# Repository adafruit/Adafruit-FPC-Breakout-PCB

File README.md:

## Adafruit FPC Breakout for Raspberry Pi 5 DSI or RP2350 HSTX - 22 Pin 0.5mm PCB

<a href="http://www.adafruit.com/products/6014"><br/>
Click here to purchase one from the Adafruit shop</a>

PCB files for the Adafruit FPC Breakout for Raspberry Pi 5 DSI or RP2350 HSTX - 22 Pin 0.5mm. 

Format is EagleCAD schematic and board layout
* https://www.adafruit.com/product/6014

### Description

This little breakout board is specifically designed for use with Raspberry Pi 5 or our RP2350 boards that have an 'HSTX' connector. These devices use a semi-standard FPC connector to pipe high speed data for video transmission over differential pairs. But maybe you want to make a custom setup or adapt to a different product? This doohickey is your pal.

Basically, you can use a 22-pin 0.5mm pitch FPC cable to connect between the two boards to get access to the four (Pi 5) or three (HSTX) differential data channels, plus the differential clock. There's also 3.3V power output, I2C, and two GPIO. We placed a fairly big ground plane and we did our best to route the signals cleanly but any time you solder wires or use a bread/perf-board with high-speed signal there's a risk of signal degradation!

Each order comes with one breakout board, 22-pin FPC cable is not included.

### License

Adafruit invests time and resources providing this open source design, please support Adafruit and open-source hardware by purchasing products from [Adafruit](https://www.adafruit.com)!

Designed by Limor Fried/Ladyada for Adafruit Industries.

Creative Commons Attribution/Share-Alike, all text above must be included in any redistribution. 
See license.txt for additional details.

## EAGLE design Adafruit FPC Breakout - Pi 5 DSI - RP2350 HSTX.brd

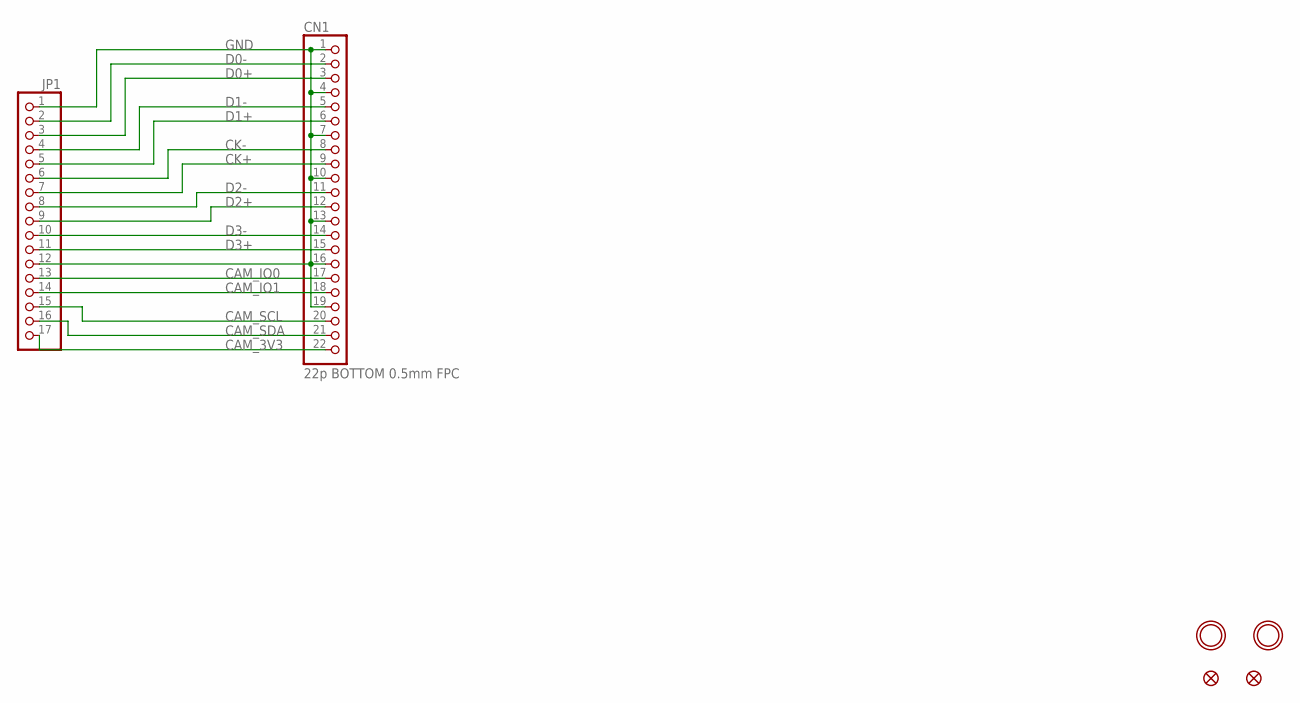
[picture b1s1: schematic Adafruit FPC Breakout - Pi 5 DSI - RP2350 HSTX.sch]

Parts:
CN1: 22p BOTTOM 0.5mm FPC; FPC_22PIN
FID1, FID2: FIDUCIAL_1MM
JP1: HEADER-1X17; 1X17_ROUND70
U$2, U$3: MOUNTINGHOLE2.5; MOUNTINGHOLE_2.5_PLATED

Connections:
CAM_3V3: CN1.22, JP1.17
CAM_IO0: CN1.17, JP1.13
CAM_IO1: CN1.18, JP1.14
CAM_SCL: CN1.20, JP1.15
CAM_SDA: CN1.21, JP1.16
CK+: CN1.9, JP1.7
CK-: CN1.8, JP1.6
D0+: CN1.3, JP1.3
D0-: CN1.2, JP1.2
D1+: CN1.6, JP1.5
D1-: CN1.5, JP1.4
D2+: CN1.12, JP1.9
D2-: CN1.11, JP1.8
D3+: CN1.15, JP1.11
D3-: CN1.14, JP1.10
GND: CN1.1, CN1.4, CN1.7, CN1.10, CN1.13, CN1.16, CN1.19, JP1.1, JP1.12

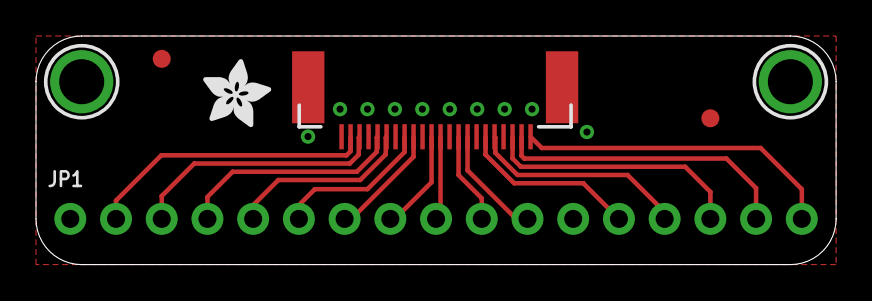
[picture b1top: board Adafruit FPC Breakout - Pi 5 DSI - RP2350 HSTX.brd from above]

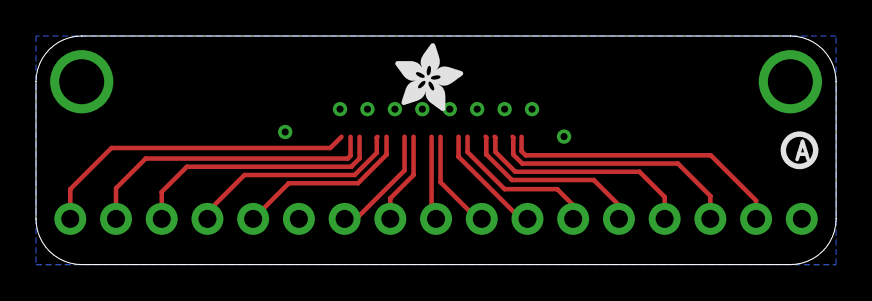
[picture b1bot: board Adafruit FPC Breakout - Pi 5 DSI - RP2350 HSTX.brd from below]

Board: 2 copper layers, 44.5 x 12.7 mm, 29 parts (3 on the bottom side), 16 nets.

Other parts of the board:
PLABEL1: PLABEL1
PLABEL2: PLABEL2
PLABEL3: PLABEL3
PLABEL4: PLABEL4
PLABEL5: PLABEL5
PLABEL6: PLABEL6
PLABEL7: PLABEL7
PLABEL8: PLABEL8
PLABEL9: PLABEL9
PLABEL10: PLABEL10
PLABEL11: PLABEL11
PLABEL12: PLABEL12
PLABEL13: PLABEL13
PLABEL14: PLABEL14
PLABEL15: PLABEL15
PLABEL16: PLABEL16
PLABEL17: PLABEL17
PLABEL18: PLABEL18
PLABEL19: PLABEL19
PLABEL20: PLABEL20
U$4, U$5: ADAFRUIT_3.5MM
U$6: PCBFEAT-REV-040

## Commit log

2024-08-23 cookiecutter

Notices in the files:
parts and their libraries:
microbuilder: This work is placed in the public domain, and may be freely used for commercial and non-commercial work with the following conditions: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
